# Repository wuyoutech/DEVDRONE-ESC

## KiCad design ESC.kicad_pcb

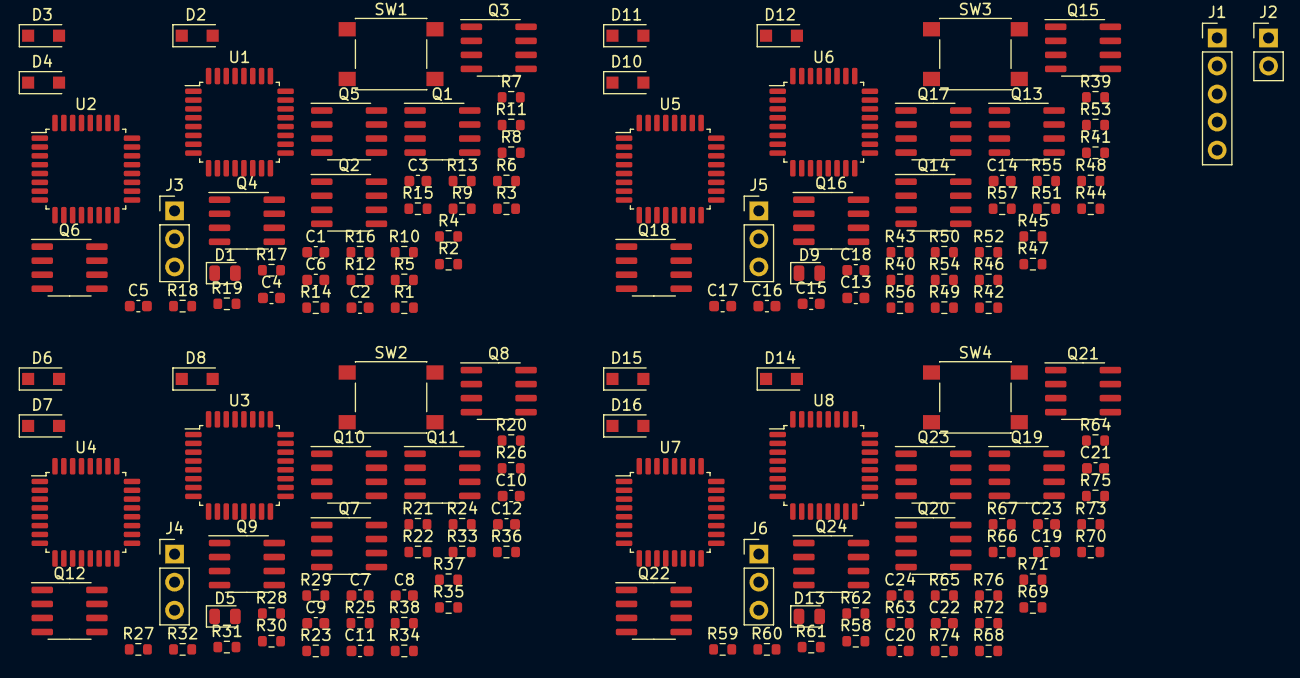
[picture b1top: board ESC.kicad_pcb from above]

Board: 2 copper layers, 158 parts (0 on the bottom side), 150 nets, no tracks yet.

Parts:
C1, C7, C13, C19: 100nF; C_0603_1608Metric
C2, C3, C4, C8, C9, C10, C14, C15, C16, C20, C21, C22: 1uF; C_0603_1608Metric
C5, C6, C11, C12, C17, C18, C23, C24: 0.1uF; C_0603_1608Metric
D1, D5, D9, D13: LED; LED_0805_2012Metric
D2, D3, D4, D6, D7, D8, D10, D11, D12, D14, D15, D16: E1J; D_SOD-123F
J1: Conn_01x05_Female; PinHeader_1x05_P2.54mm_Vertical
J2: Conn_01x02_Male; PinHeader_1x02_P2.54mm_Vertical
J3, J4, J5, J6: SWD; PinHeader_1x03_P2.54mm_Vertical
Q1, Q2, Q3, Q4, Q5, Q6, Q7, Q8, Q9, Q10, Q11, Q12, Q13, Q14, Q15, Q16, Q17, Q18, Q19, Q20, Q21, Q22, Q23, Q24: Si4162DY; SOIC-8_3.9x4.9mm_P1.27mm
R1, R3, R4, R7, R10, R12, R15, R17, R20, R22, R23, R26, R29, R31, R34, R36, R39, R41, R42, R45, R48, R50, R53, R55, R58, R60, R61, R64, R67, R69, R72, R74: 10K; R_0603_1608Metric
R2, R21, R40, R59: 330R; R_0603_1608Metric
R5, R24, R43, R62: 2.2K; R_0603_1608Metric
R6, R11, R16, R25, R30, R35, R44, R49, R54, R63, R68, R73: 50K; R_0603_1608Metric
R8, R9, R13, R14, R18, R19, R27, R28, R32, R33, R37, R38, R46, R47, R51, R52, R56, R57, R65, R66, R70, R71, R75, R76: 10R; R_0603_1608Metric
SW1, SW2, SW3, SW4: SW_Push; SW_Push_1P1T_NO_6x6mm_H9.5mm
U1, U3, U5, U7: FD6288Q; LQFP-32_7x7mm_P0.8mm
U2, U4, U6, U8: STM32F051K6Tx; LQFP-32_7x7mm_P0.8mm

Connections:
+3V3: C1.1, C5.1, C6.1, C7.1, C11.1, C12.1, C13.1, C17.1, C18.1, C19.1, C23.1, C24.1, D1.2, D2.2, D3.2, D4.2, D5.2, D6.2, D7.2, D8.2, D9.2, D10.2, D11.2, D12.2, D13.2, D14.2, D15.2, D16.2, J2.1, Q1.5, Q1.6, Q1.7, Q1.8, Q3.5, Q3.6, Q3.7, Q3.8, Q5.5, Q5.6, Q5.7, Q5.8, Q7.5, Q7.6, Q7.7, Q7.8, Q9.5, Q9.6, Q9.7, Q9.8, Q11.5, Q11.6, Q11.7, Q11.8, Q13.5, Q13.6, Q13.7, Q13.8, Q15.5, Q15.6, Q15.7, Q15.8, Q17.5, Q17.6, Q17.7, Q17.8, Q19.5, Q19.6, Q19.7, Q19.8, Q21.5, Q21.6, Q21.7, Q21.8, Q23.5, Q23.6, Q23.7, Q23.8, R3.1, R22.1, R41.1, R60.1, U1.4, U2.1, U2.5, U2.17, U3.4, U4.1, U4.5, U4.17, U5.4, U6.1, U6.5, U6.17, U7.4, U8.1, U8.5, U8.17
/ECS1/AH: U1.22, U2.20
/ECS1/AL: U1.1, U2.15
/ECS1/BH: U1.23, U2.19
/ECS1/BL: U1.2, U2.14
/ECS1/CH: U1.24, U2.18
/ECS1/PWM: J1.5, R5.1
/ECS2/AH: U3.22, U4.20
/ECS2/AL: U3.1, U4.15
/ECS2/BH: U3.23, U4.19
/ECS2/BL: U3.2, U4.14
/ECS2/CH: U3.24, U4.18
/ECS2/PWM: J1.4, R24.1
/ECS3/AH: U5.22, U6.20
/ECS3/AL: U5.1, U6.15
/ECS3/BH: U5.23, U6.19
/ECS3/BL: U5.2, U6.14
/ECS3/CH: U5.24, U6.18
/ECS3/PWM: J1.3, R43.1
/ECS4/AH: U7.22, U8.20
/ECS4/AL: U7.1, U8.15
/ECS4/BH: U7.23, U8.19
/ECS4/BL: U7.2, U8.14
/ECS4/CH: U7.24, U8.18
/ECS4/PWM: J1.2, R62.1
GND: C1.2, C5.2, C6.2, C7.2, C11.2, C12.2, C13.2, C17.2, C18.2, C19.2, C23.2, C24.2, J1.1, J2.2, J3.3, J4.3, J5.3, J6.3, Q2.1, Q2.2, Q2.3, Q4.1, Q4.2, Q4.3, Q6.1, Q6.2, Q6.3, Q8.1, Q8.2, Q8.3, Q10.1, Q10.2, Q10.3, Q12.1, Q12.2, Q12.3, Q14.1, Q14.2, Q14.3, Q16.1, Q16.2, Q16.3, Q18.1, Q18.2, Q18.3, Q20.1, Q20.2, Q20.3, Q22.1, Q22.2, Q22.3, Q24.1, Q24.2, Q24.3, R1.2, R2.2, R20.2, R21.2, R39.2, R40.2, R58.2, R59.2, SW1.1, SW2.1, SW3.1, SW4.1, U1.6, U2.16, U2.32, U3.6, U4.16, U4.32, U5.6, U6.16, U6.32, U7.6, U8.16, U8.32
unnamed: C2.1, D2.1, U1.20
unnamed: C2.2, Q5.1, Q5.2, Q5.3, Q6.5, Q6.6, Q6.7, Q6.8, R16.1, U1.18
unnamed: C3.1, D3.1, D4.1, U1.17
unnamed: C3.2, Q3.1, Q3.2, Q3.3, Q4.5, Q4.6, Q4.7, Q4.8, R11.1, U1.15
unnamed: C4.1, U1.14
unnamed: C4.2, Q1.1, Q1.2, Q1.3, Q2.5, Q2.6, Q2.7, Q2.8, R6.1, U1.12
unnamed: C8.1, D6.1, U3.20
unnamed: C8.2, Q11.1, Q11.2, Q11.3, Q12.5, Q12.6, Q12.7, Q12.8, R35.1, U3.18
unnamed: C9.1, D7.1, D8.1, U3.17
unnamed: C9.2, Q9.1, Q9.2, Q9.3, Q10.5, Q10.6, Q10.7, Q10.8, R30.1, U3.15
unnamed: C10.1, U3.14
unnamed: C10.2, Q7.1, Q7.2, Q7.3, Q8.5, Q8.6, Q8.7, Q8.8, R25.1, U3.12
unnamed: C14.1, D10.1, U5.20
unnamed: C14.2, Q17.1, Q17.2, Q17.3, Q18.5, Q18.6, Q18.7, Q18.8, R54.1, U5.18
unnamed: C15.1, D11.1, D12.1, U5.17
unnamed: C15.2, Q15.1, Q15.2, Q15.3, Q16.5, Q16.6, Q16.7, Q16.8, R49.1, U5.15
unnamed: C16.1, U5.14
unnamed: C16.2, Q13.1, Q13.2, Q13.3, Q14.5, Q14.6, Q14.7, Q14.8, R44.1, U5.12
unnamed: C20.1, D14.1, U7.20
unnamed: C20.2, Q23.1, Q23.2, Q23.3, Q24.5, Q24.6, Q24.7, Q24.8, R73.1, U7.18
unnamed: C21.1, D15.1, D16.1, U7.17
unnamed: C21.2, Q21.1, Q21.2, Q21.3, Q22.5, Q22.6, Q22.7, Q22.8, R68.1, U7.15
unnamed: C22.1, U7.14
unnamed: C22.2, Q19.1, Q19.2, Q19.3, Q20.5, Q20.6, Q20.7, Q20.8, R63.1, U7.12
unnamed: D1.1, R2.1
unnamed: D5.1, R21.1
unnamed: D9.1, R40.1
unnamed: D13.1, R59.1
unnamed: J3.1, U2.24
unnamed: J3.2, U2.23
unnamed: J4.1, U4.24
unnamed: J4.2, U4.23
unnamed: J5.1, U6.24
unnamed: J5.2, U6.23
unnamed: J6.1, U8.24
unnamed: J6.2, U8.23
unnamed: Q1.4, R8.1
unnamed: Q2.4, R9.1
unnamed: Q3.4, R13.1
unnamed: Q4.4, R14.1
unnamed: Q5.4, R18.1
unnamed: Q6.4, R19.1
unnamed: Q7.4, R27.1
unnamed: Q8.4, R28.1
unnamed: Q9.4, R32.1
unnamed: Q10.4, R33.1
unnamed: Q11.4, R37.1
unnamed: Q12.4, R38.1
unnamed: Q13.4, R46.1
unnamed: Q14.4, R47.1
unnamed: Q15.4, R51.1
unnamed: Q16.4, R52.1
unnamed: Q17.4, R56.1
unnamed: Q18.4, R57.1
unnamed: Q19.4, R65.1
unnamed: Q20.4, R66.1
unnamed: Q21.4, R70.1
unnamed: Q22.4, R71.1
unnamed: Q23.4, R75.1
unnamed: Q24.4, R76.1
unnamed: R1.1, U2.31
unnamed: R3.2, SW1.2, U2.4
unnamed: R4.1, R6.2, R7.1
unnamed: R4.2, U2.11
unnamed: R5.2, U2.8
unnamed: R8.2, U1.13
unnamed: R9.2, U1.9
unnamed: R10.1, R11.2, R12.1
unnamed: R10.2, U2.10
unnamed: R7.2, R12.2, R17.2, U2.7
unnamed: R13.2, U1.16
unnamed: R14.2, U1.10
unnamed: R15.1, R16.2, R17.1
unnamed: R15.2, U2.6
unnamed: R18.2, U1.19
unnamed: R19.2, U1.11
unnamed: R20.1, U4.31
unnamed: R22.2, SW2.2, U4.4
unnamed: R23.1, R25.2, R26.1
unnamed: R23.2, U4.11
unnamed: R24.2, U4.8
unnamed: R26.2, R31.2, R36.2, U4.7
unnamed: R27.2, U3.13
unnamed: R28.2, U3.9
unnamed: R29.1, R30.2, R31.1
unnamed: R29.2, U4.10
unnamed: R32.2, U3.16
unnamed: R33.2, U3.10
unnamed: R34.1, R35.2, R36.1
unnamed: R34.2, U4.6
unnamed: R37.2, U3.19
unnamed: R38.2, U3.11
unnamed: R39.1, U6.31
unnamed: R41.2, SW3.2, U6.4
unnamed: R42.1, R44.2, R45.1
unnamed: R42.2, U6.11
unnamed: R43.2, U6.8
unnamed: R45.2, R50.2, R55.2, U6.7
unnamed: R46.2, U5.13
unnamed: R47.2, U5.9
unnamed: R48.1, R49.2, R50.1
unnamed: R48.2, U6.10
unnamed: R51.2, U5.16
unnamed: R52.2, U5.10
unnamed: R53.1, R54.2, R55.1
unnamed: R53.2, U6.6
unnamed: R56.2, U5.19
unnamed: R57.2, U5.11
unnamed: R58.1, U8.31
unnamed: R60.2, SW4.2, U8.4
unnamed: R61.1, R63.2, R64.1
unnamed: R61.2, U8.11
unnamed: R62.2, U8.8
unnamed: R64.2, R69.2, R74.2, U8.7
unnamed: R65.2, U7.13
unnamed: R66.2, U7.9
unnamed: R67.1, R68.2, R69.1
unnamed: R67.2, U8.10
unnamed: R70.2, U7.16
unnamed: R71.2, U7.10
unnamed: R72.1, R73.2, R74.1
unnamed: R72.2, U8.6
unnamed: R75.2, U7.19
unnamed: R76.2, U7.11

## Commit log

2021-08-21 Initialize Commit
2021-08-21 ADD README
